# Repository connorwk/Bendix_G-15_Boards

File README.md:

# Bendix G-15 Boards
KiCad re-creations of the schematics and boards for the Bendix G-15.

These boards are meant to be functional drop in replacements for the original boards, whether they are damaged or missing.
The idea is either:
- To drill out the rivets on the original card's frames, desolder the wires for the tube sockets/etc and rivet/solder in the new board.
- Build up oragami PCBs to build a card frame.

Currently the goal is to get all schematics and boards layed out for the G-15 CPU and get a CPU at the System Source Computer Museum up and running using replacement boards.

## TODO
- Find suitable replacement diodes/transistors. This will be determined by component parameter analysis, specification comparison, and functional testing of boards with replaced components.
- Add oragami PCBs to allow building your own card handles to assemble around the boards.

## References
Documentation for the Bendix G-15 can be found here:
http://bitsavers.org/pdf/bendix/g-15/

The document used for schematics is:
http://bitsavers.org/pdf/bendix/g-15/G15D_Tech_Man_Rev1_Part1.pdf

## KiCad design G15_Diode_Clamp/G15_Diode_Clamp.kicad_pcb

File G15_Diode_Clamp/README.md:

# Diode ClamP, For Bendix G-15 CPU
[Schematic](G15_Diode_Clamp_Schematic.pdf)

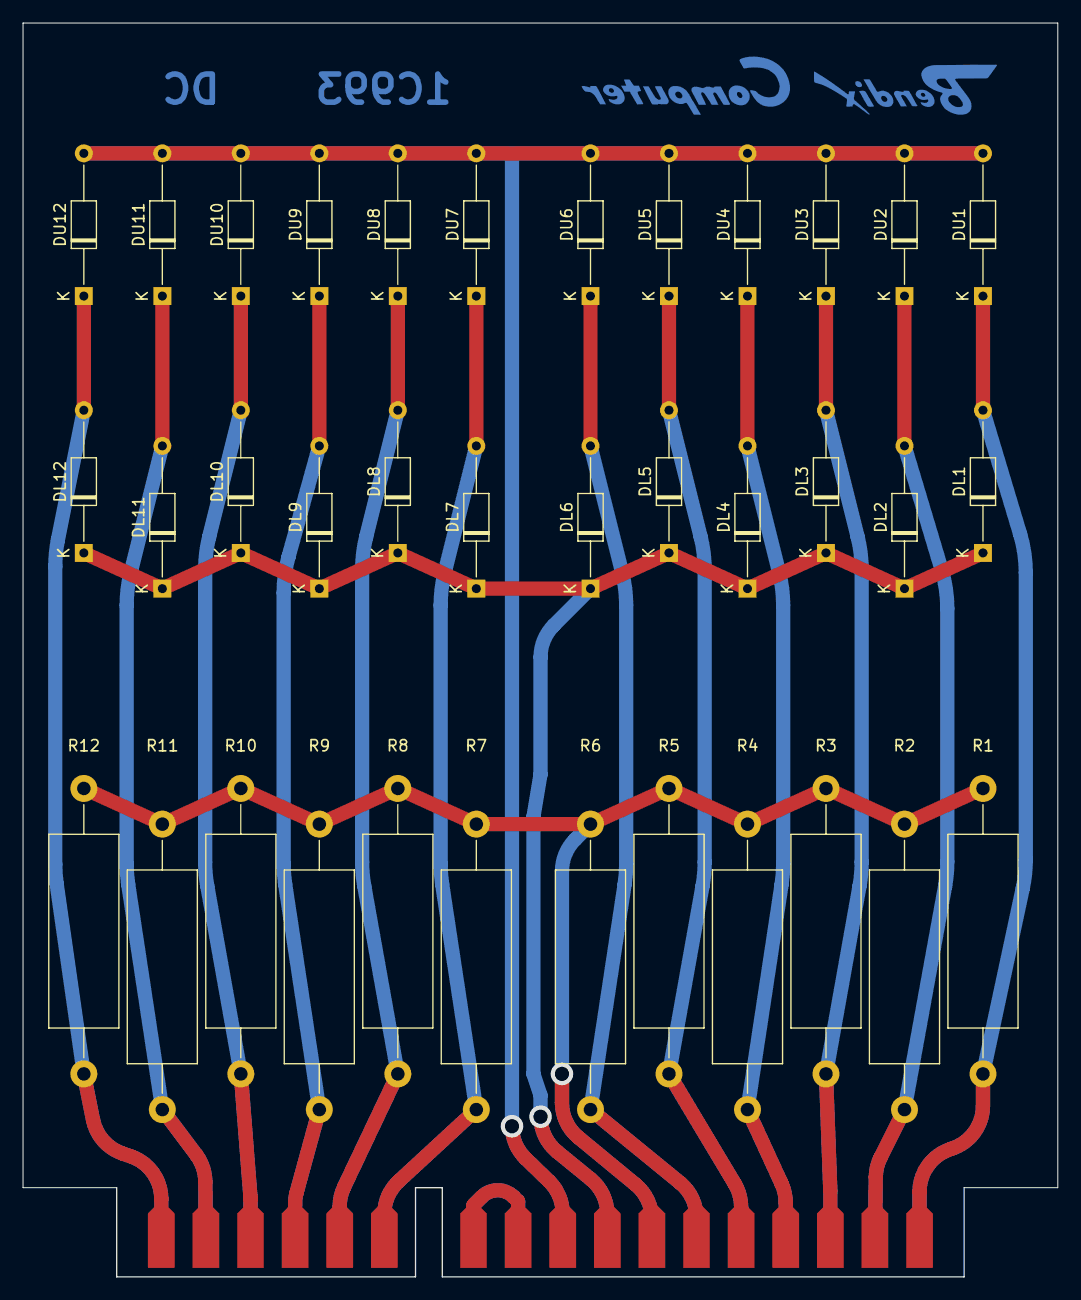
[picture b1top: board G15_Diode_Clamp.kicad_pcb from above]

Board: 2 copper layers, 92.1 x 111.6 mm, 37 parts (0 on the bottom side), 17 nets.

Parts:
DL1, DL2, DL3, DL4, DL5, DL6, DL7, DL8, DL9, DL10, DL11, DL12: 1N4007; D_DO-35_SOD27_P12.70mm_Horizontal
DU1, DU2, DU3, DU4, DU5, DU6, DU7, DU8, DU9, DU10, DU11, DU12: 1N4007; D_DO-35_SOD27_P12.70mm_Horizontal
J1: Conn_02x18_Row_Letter_First; Card_Edge_N_Key
R1, R2, R3, R4, R5, R6, R7, R8, R9, R10, R11, R12: 39K 1W 5%; R_Axial_DIN0617_L17.0mm_D6.0mm_P25.40mm_Horizontal

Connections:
/+100V: J1.a7, J1.b7, R1.2, R2.2, R3.2, R4.2, R5.2, R6.2, R7.2, R8.2, R9.2, R10.2, R11.2, R12.2
/-20V: DU1.2 (A), DU2.2 (A), DU3.2 (A), DU4.2 (A), DU5.2 (A), DU6.2 (A), DU7.2 (A), DU8.2 (A), DU9.2 (A), DU10.2 (A), DU11.2 (A), DU12.2 (A), J1.a9, J1.b9
/CL_{1}: DL1.2 (A), DU1.1 (K), J1.a1, J1.b1, R1.1
/CL_{2}: DL2.2 (A), DU2.1 (K), J1.a2, J1.b2, R2.1
/CL_{3}: DL3.2 (A), DU3.1 (K), J1.a3, J1.b3, R3.1
/CL_{4}: DL4.2 (A), DU4.1 (K), J1.a4, J1.b4, R4.1
/CL_{5}: DL5.2 (A), DU5.1 (K), J1.a5, J1.b5, R5.1
/CL_{6}: DL6.2 (A), DU6.1 (K), J1.a6, J1.b6, R6.1
/CL_{7}: DL7.2 (A), DU7.1 (K), J1.a13, J1.b13, R7.1
/CL_{8}: DL8.2 (A), DU8.1 (K), J1.a14, J1.b14, R8.1
/CL_{9}: DL9.2 (A), DU9.1 (K), J1.a15, J1.b15, R9.1
/CL_{10}: DL10.2 (A), DU10.1 (K), J1.a16, J1.b16, R10.1
/CL_{11}: DL11.2 (A), DU11.1 (K), J1.a17, J1.b17, R11.1
/CL_{12}: DL12.2 (A), DU12.1 (K), J1.a18, J1.b18, R12.1
GND: DL1.1 (K), DL2.1 (K), DL3.1 (K), DL4.1 (K), DL5.1 (K), DL6.1 (K), DL7.1 (K), DL8.1 (K), DL9.1 (K), DL10.1 (K), DL11.1 (K), DL12.1 (K), J1.a8, J1.b8
unnamed: J1.a10, J1.a11
unnamed: J1.b10, J1.b11

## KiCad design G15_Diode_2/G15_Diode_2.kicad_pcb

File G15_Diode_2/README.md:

# Diode 2, For Bendix G-15 CPU
[Schematic](G15_Diode_2_Schematic.pdf)

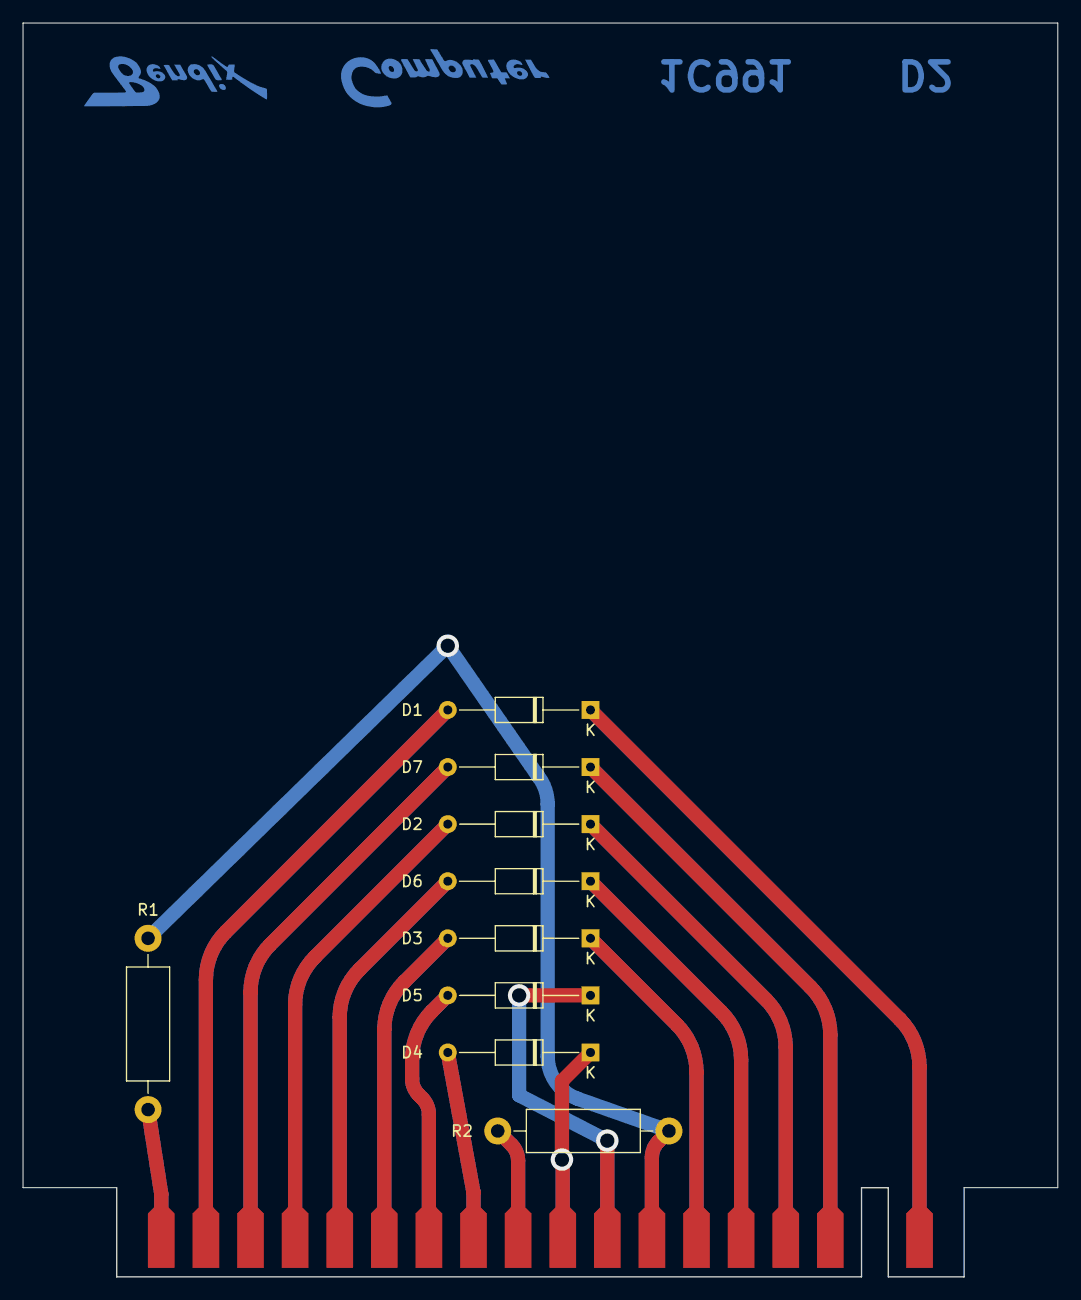
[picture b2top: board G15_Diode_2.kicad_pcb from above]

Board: 2 copper layers, 92.1 x 111.6 mm, 10 parts (0 on the bottom side), 17 nets.

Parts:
D1, D2, D3, D4, D5, D6, D7: 1N4007; D_DO-35_SOD27_P12.70mm_Horizontal
J1: Conn_02x18_Row_Letter_First; Card_Edge_B_Key
R1, R2: 110K 1/2W 5%; R_Axial_DIN0411_L9.9mm_D3.6mm_P15.24mm_Horizontal

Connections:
/110K to B+_{1}: J1.a18, J1.b18, R1.1
/110K to B+_{2}: J1.a10, J1.b10, R2.1
/+100V: J1.a7, J1.b7, R1.2, R2.2
/C_{1}: D1.1 (K), J1.a1, J1.b1
/C_{2}: D2.1 (K), J1.a4, J1.b4
/C_{3}: D3.1 (K), J1.a6, J1.b6
/C_{4}: D4.1 (K), J1.a9, J1.b9
/C_{5}: D5.1 (K), J1.a8, J1.b8
/C_{6}: D6.1 (K), J1.a5, J1.b5
/C_{7}: D7.1 (K), J1.a3, J1.b3
/P_{1}: D1.2 (A), J1.a17, J1.b17
/P_{2}: D2.2 (A), J1.a15, J1.b15
/P_{3}: D3.2 (A), J1.a13, J1.b13
/P_{4}: D4.2 (A), J1.a11, J1.b11
/P_{5}: D5.2 (A), J1.a12, J1.b12
/P_{6}: D6.2 (A), J1.a14, J1.b14
/P_{7}: D7.2 (A), J1.a16, J1.b16

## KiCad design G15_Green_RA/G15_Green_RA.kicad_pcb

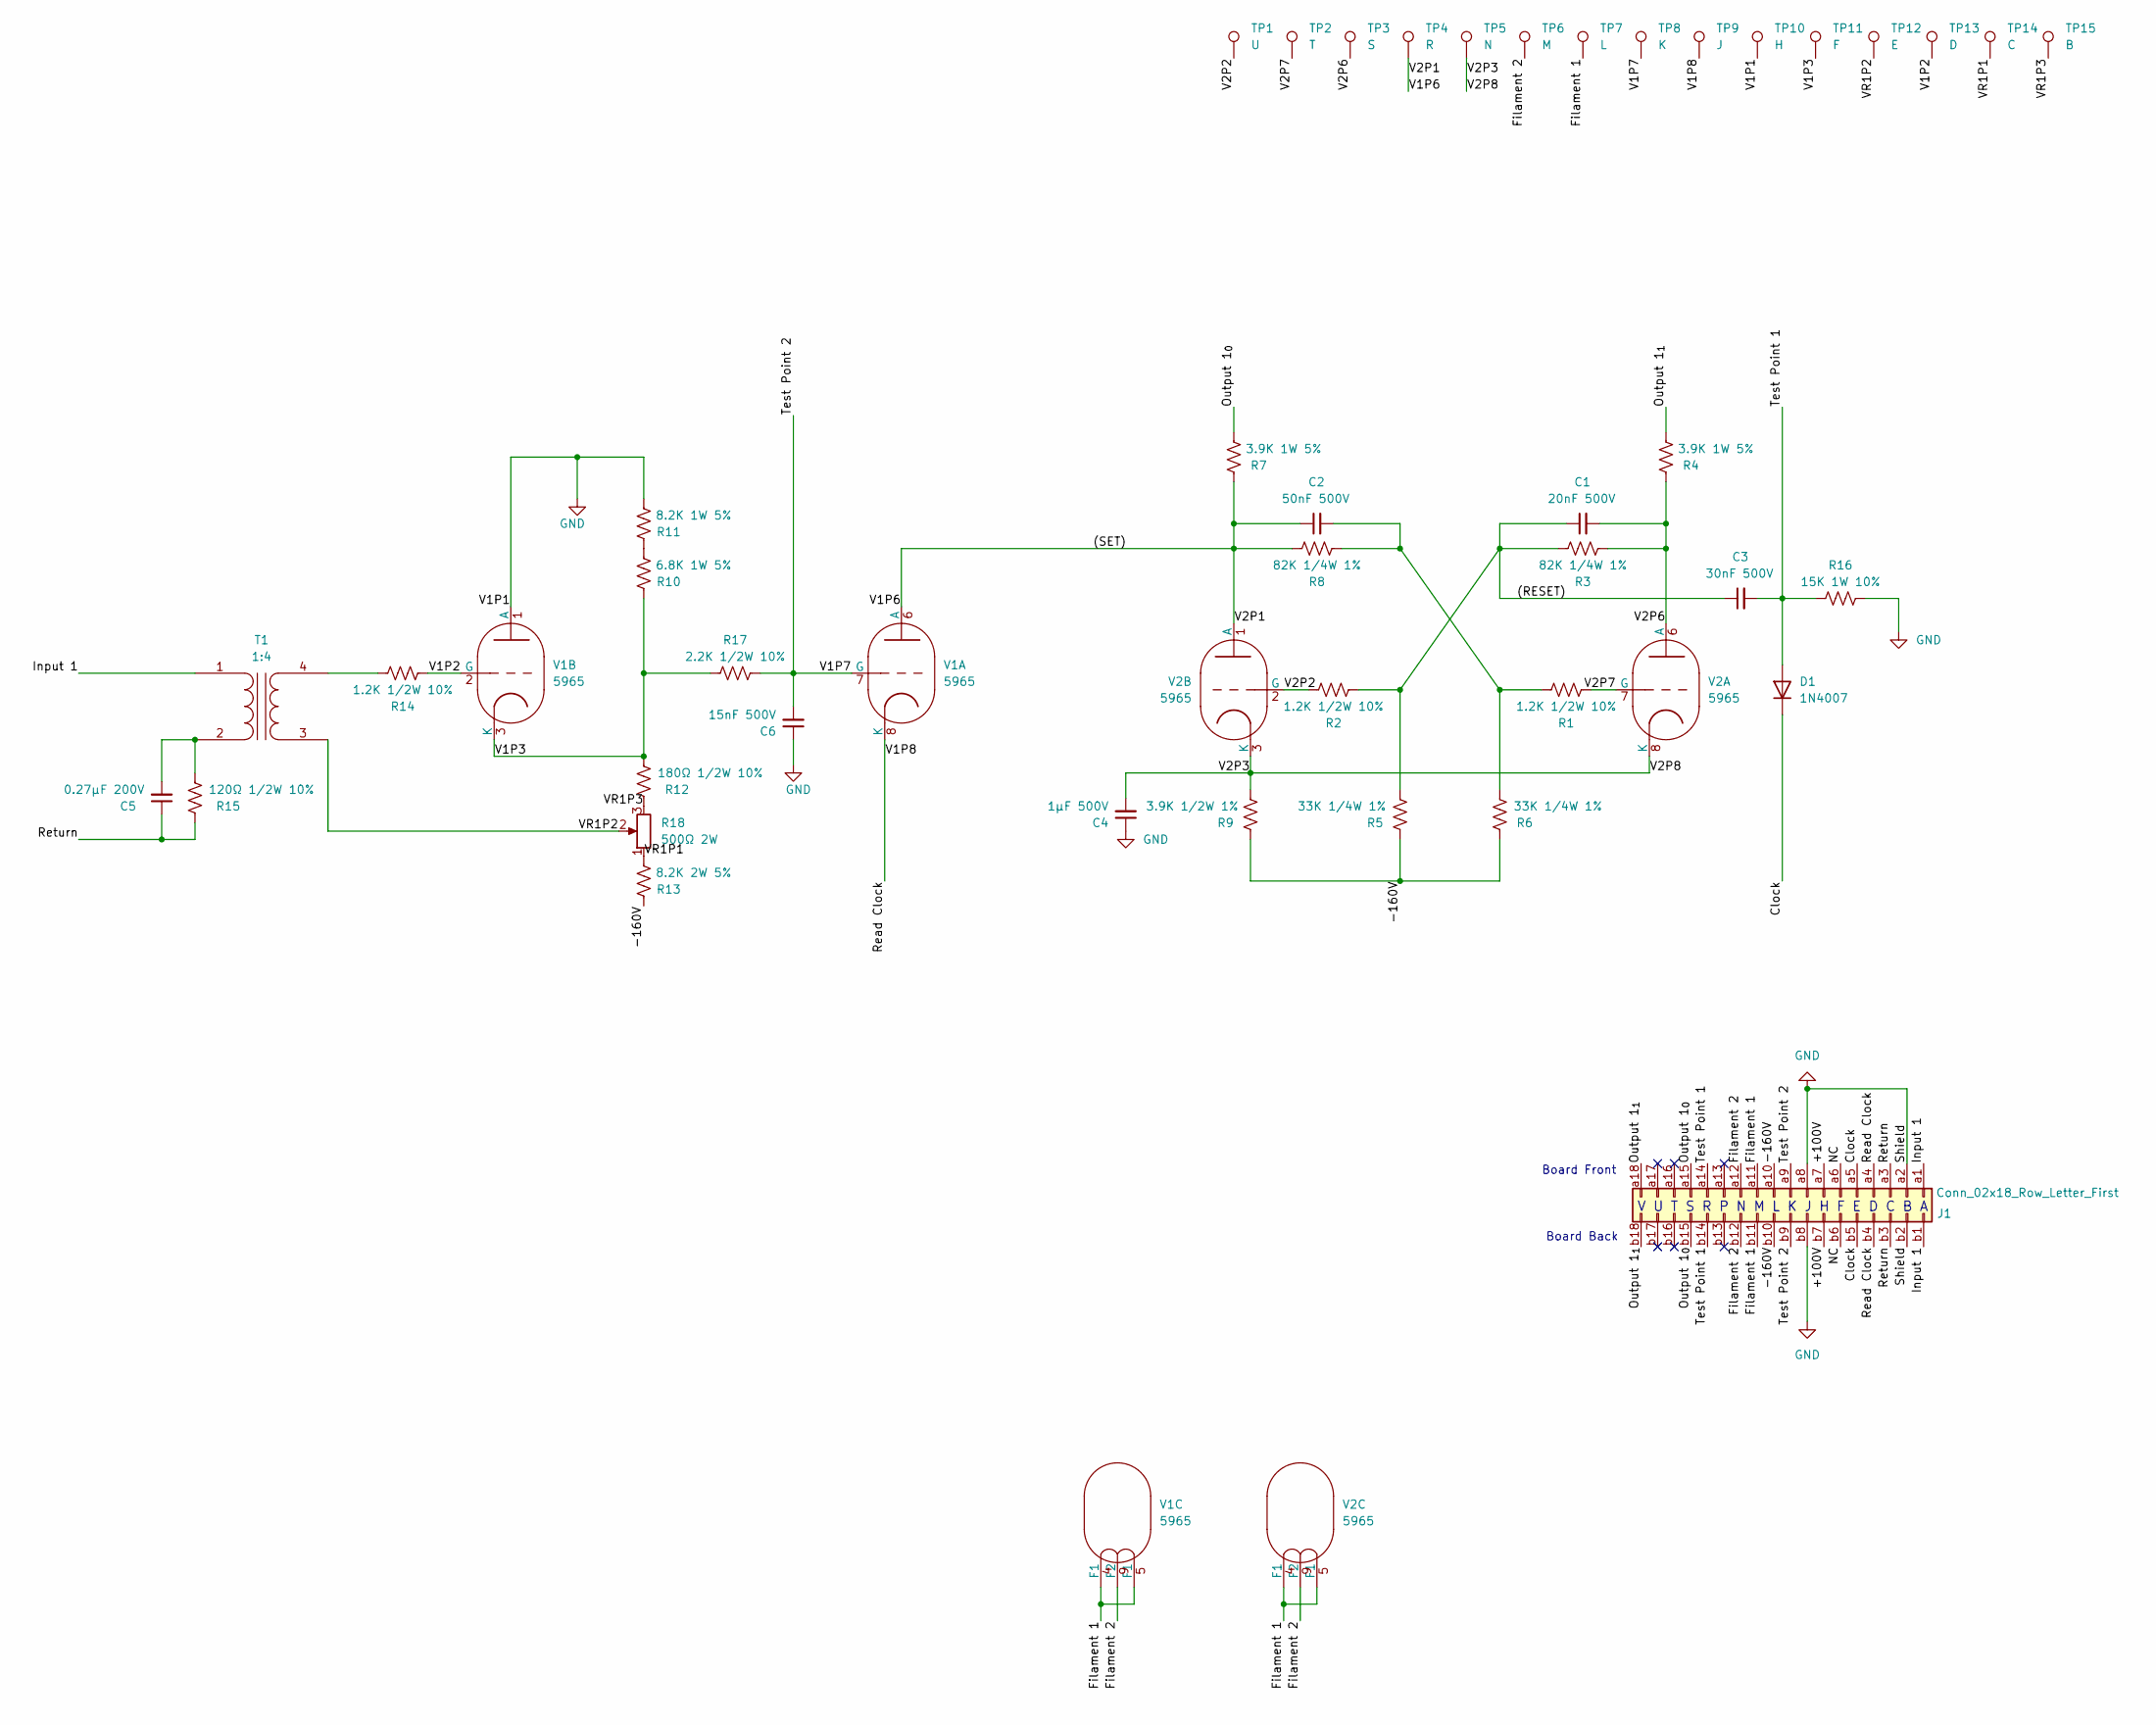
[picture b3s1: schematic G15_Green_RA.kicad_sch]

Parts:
C1: 20nF 500V; C_Axial_L12.0mm_D6.5mm_P20.00mm_Horizontal
C2: 50nF 500V; C_Axial_L12.0mm_D6.5mm_P20.00mm_Horizontal
C3: 30nF 500V; C_Axial_L12.0mm_D6.5mm_P20.00mm_Horizontal
C4: 1µF 500V; C_Axial_L12.0mm_D6.5mm_P20.00mm_Horizontal
C5: 0.27µF 200V; C_Axial_L22.0mm_D10.5mm_P27.50mm_Horizontal
C6: 15nF 500V; C_Axial_L12.0mm_D6.5mm_P20.00mm_Horizontal
D1: 1N4007; D_DO-35_SOD27_P12.70mm_Horizontal
J1: Conn_02x18_Row_Letter_First; Card_Edge_F_Key
R1, R2, R14: 1.2K 1/2W 10%; R_Axial_DIN0411_L9.9mm_D3.6mm_P15.24mm_Horizontal
R3, R8: 82K 1/4W 1%; R_Axial_DIN0516_L15.5mm_D5.0mm_P20.32mm_Horizontal
R4, R7: 3.9K 1W 5%; R_Axial_DIN0516_L15.5mm_D5.0mm_P20.32mm_Horizontal
R5, R6: 33K 1/4W 1%; R_Axial_DIN0516_L15.5mm_D5.0mm_P20.32mm_Horizontal
R9: 3.9K 1/2W 1%; R_Axial_DIN0617_L17.0mm_D6.0mm_P25.40mm_Horizontal
R10: 6.8K 1W 5%; R_Axial_DIN0516_L15.5mm_D5.0mm_P20.32mm_Horizontal
R11: 8.2K 1W 5%; R_Axial_DIN0516_L15.5mm_D5.0mm_P20.32mm_Horizontal
R12: 180Ω 1/2W 10%; R_Axial_DIN0411_L9.9mm_D3.6mm_P15.24mm_Horizontal
R13: 8.2K 2W 5%; R_Axial_DIN0918_L18.0mm_D9.0mm_P22.86mm_Horizontal
R15: 120Ω 1/2W 10%; R_Axial_DIN0411_L9.9mm_D3.6mm_P15.24mm_Horizontal
R16: 15K 1W 10%; R_Axial_DIN0614_L14.3mm_D5.7mm_P25.40mm_Horizontal
R17: 2.2K 1/2W 10%; R_Axial_DIN0411_L9.9mm_D3.6mm_P15.24mm_Horizontal
R18: 500Ω 2W
T1: 1:4; Transformer_Toroid_Horizontal_D14.0mm_Amidon-T50
TP1: U; TestPoint_Plated_Hole_D2.0mm
TP2: T; TestPoint_Plated_Hole_D2.0mm
TP3: S; TestPoint_Plated_Hole_D2.0mm
TP4: R; TestPoint_Plated_Hole_D2.0mm
TP5: N; TestPoint_Plated_Hole_D2.0mm
TP6: M; TestPoint_Plated_Hole_D2.0mm
TP7: L; TestPoint_Plated_Hole_D2.0mm
TP8: K; TestPoint_Plated_Hole_D2.0mm
TP9: J; TestPoint_Plated_Hole_D2.0mm
TP10: H; TestPoint_Plated_Hole_D2.0mm
TP11: F; TestPoint_Plated_Hole_D2.0mm
TP12: E; TestPoint_Plated_Hole_D2.0mm
TP13: D; TestPoint_Plated_Hole_D2.0mm
TP14: C; TestPoint_Plated_Hole_D2.0mm
TP15: B; TestPoint_Plated_Hole_D2.0mm
V1, V2: 5965

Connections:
/(RESET): C1.1, C3.1, R2.1, R3.2, R5.1
/(SET): C2.1, R7.2, R8.2, TP4.1, V1.6 (A), V2.1 (A)
/+100V: J1.a7, J1.b7
/-160V: J1.a10, J1.b10, R5.2, R6.2, R9.2, R13.2
/Clock: D1.1 (K), J1.a5, J1.b5
/Filament 1: J1.a11, J1.b11, TP7.1, V1.4 (F1), V1.5 (F1), V2.4 (F1), V2.5 (F1)
/Filament 2: J1.a12, J1.b12, TP6.1, V1.9 (F2), V2.9 (F2)
/Input 1: J1.a1, J1.b1, T1.1 (AA)
/Output 1_{0}: J1.a15, J1.b15, R7.1
/Output 1_{1}: J1.a18, J1.b18, R4.1
/Read Clock: J1.a4, J1.b4, TP9.1, V1.8 (K)
/Return: C5.1, J1.a3, J1.b3, R15.2
/Test Point 1: C3.2, D1.2 (A), J1.a14, J1.b14, R16.1
/V1P2: R14.1, TP13.1, V1.2 (G)
/V1P3: R10.2, R12.1, R17.1, TP11.1, V1.3 (K)
/V1P7: C6.2, J1.a9, J1.b9, R17.2, TP8.1, V1.7 (G)
/V2P2: R2.2, TP1.1, V2.2 (G)
/V2P3: C4.2, R9.1, TP5.1, V2.3 (K), V2.8 (K)
/V2P6: C1.2, R3.1, R4.2, TP3.1, V2.6 (A)
/V2P7: R1.1, TP2.1, V2.7 (G)
/VR1P1: R13.1, R18.1, TP14.1
/VR1P2: R18.2, T1.3 (SA), TP12.1
/VR1P3: R12.2, R18.3, TP15.1
GND: C4.1, C6.1, J1.a2, J1.a8, J1.b2, J1.b8, R11.1, R16.2, TP10.1, V1.1 (A)
unnamed: C2.2, R1.2, R6.1, R8.1
unnamed: C5.2, R15.1, T1.2 (AB)
unnamed: R10.1, R11.2
unnamed: R14.2, T1.4 (SB)

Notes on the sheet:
Board Back
Board Front
V U T S R P N M L K J H F E D C B A

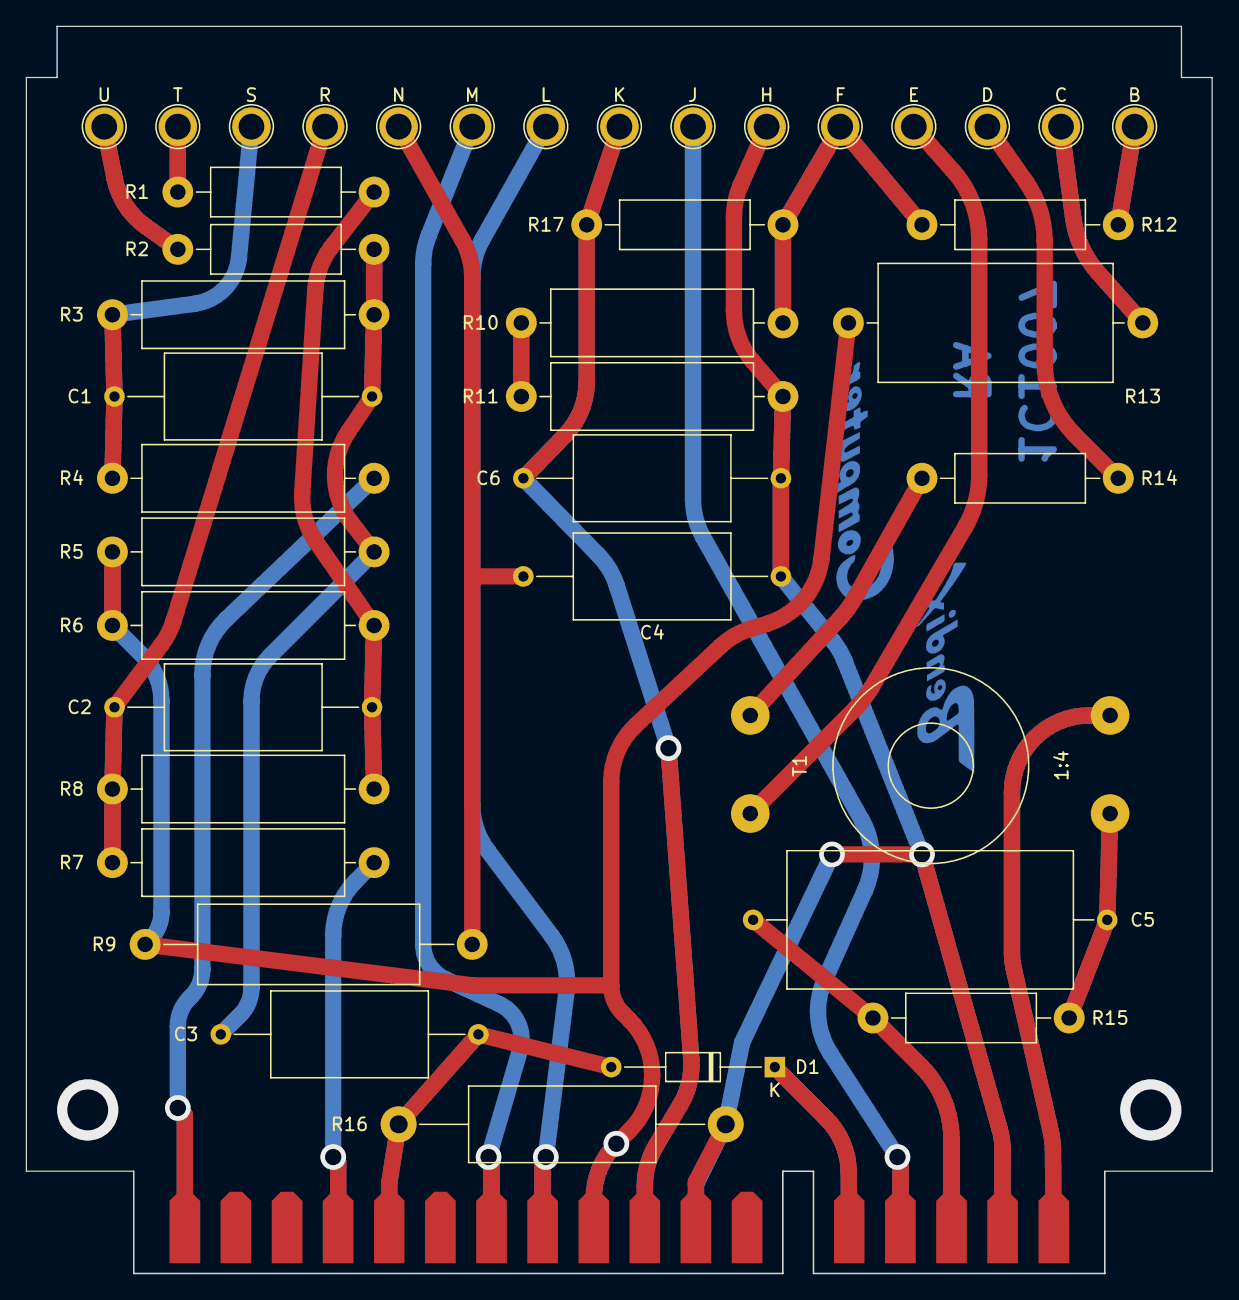
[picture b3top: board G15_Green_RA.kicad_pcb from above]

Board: 2 copper layers, 92.1 x 96.8 mm, 41 parts (0 on the bottom side), 28 nets.

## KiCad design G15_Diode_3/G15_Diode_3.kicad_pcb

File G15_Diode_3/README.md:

# Diode 3, For Bendix G-15 CPU
[Schematic](G15_Diode_3_Schematic.pdf)

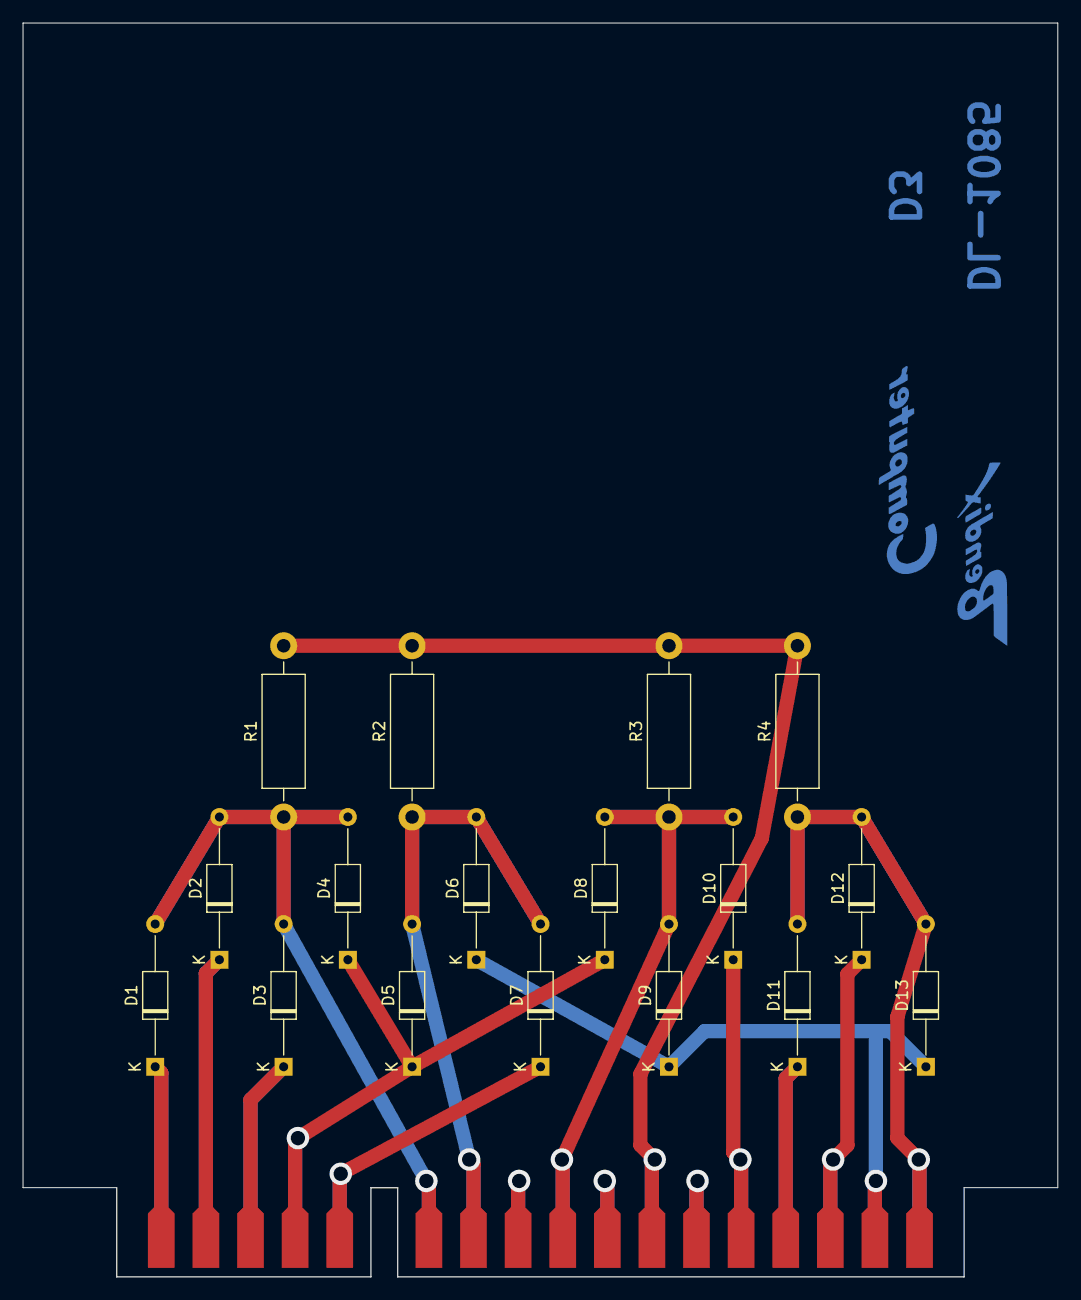
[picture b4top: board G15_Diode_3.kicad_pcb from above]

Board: 2 copper layers, 92.1 x 111.6 mm, 18 parts (0 on the bottom side), 17 nets.

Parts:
D1, D2, D3, D4, D5, D6, D7, D8, D9, D10, D11, D12, D13: 1N4007; D_DO-35_SOD27_P12.70mm_Horizontal
J1: Conn_02x18_Row_Letter_First; Card_Edge_P_Key
R1, R2, R3, R4: 110K 1/2W 5%; R_Axial_DIN0411_L9.9mm_D3.6mm_P15.24mm_Horizontal

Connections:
/+100V: J1.a7, J1.b7, R1.2, R2.2, R3.2, R4.2
/C_{1}: D1.1 (K), J1.a18, J1.b18
/C_{2}: D2.1 (K), J1.a17, J1.b17
/C_{3}: D3.1 (K), J1.a16, J1.b16
/C_{4,5,8}: D4.1 (K), D5.1 (K), D8.1 (K), J1.a15, J1.b15
/C_{6,9,13}: D6.1 (K), D9.1 (K), D13.1 (K), J1.a2, J1.b2
/C_{7}: D7.1 (K), J1.a14, J1.b14
/C_{10}: D10.1 (K), J1.a5, J1.b5
/C_{11}: D11.1 (K), J1.a4, J1.b4
/C_{12}: D12.1 (K), J1.a3, J1.b3
/NC1: J1.a10, J1.b10
/NC2: J1.a8, J1.b8
/NC3: J1.a6, J1.b6
/P_{1,2,3,4}: D1.2 (A), D2.2 (A), D3.2 (A), D4.2 (A), J1.a12, J1.b12, R1.1
/P_{5,6,7}: D5.2 (A), D6.2 (A), D7.2 (A), J1.a11, J1.b11, R2.1
/P_{8,9,10}: D8.2 (A), D9.2 (A), D10.2 (A), J1.a9, J1.b9, R3.1
/P_{11,12,13}: D11.2 (A), D12.2 (A), D13.2 (A), J1.a1, J1.b1, R4.1

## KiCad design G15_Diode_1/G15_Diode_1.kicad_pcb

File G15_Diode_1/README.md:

# Diode 1, For Bendix G-15 CPU
[Schematic](G15_Diode_1_Schematic.pdf)

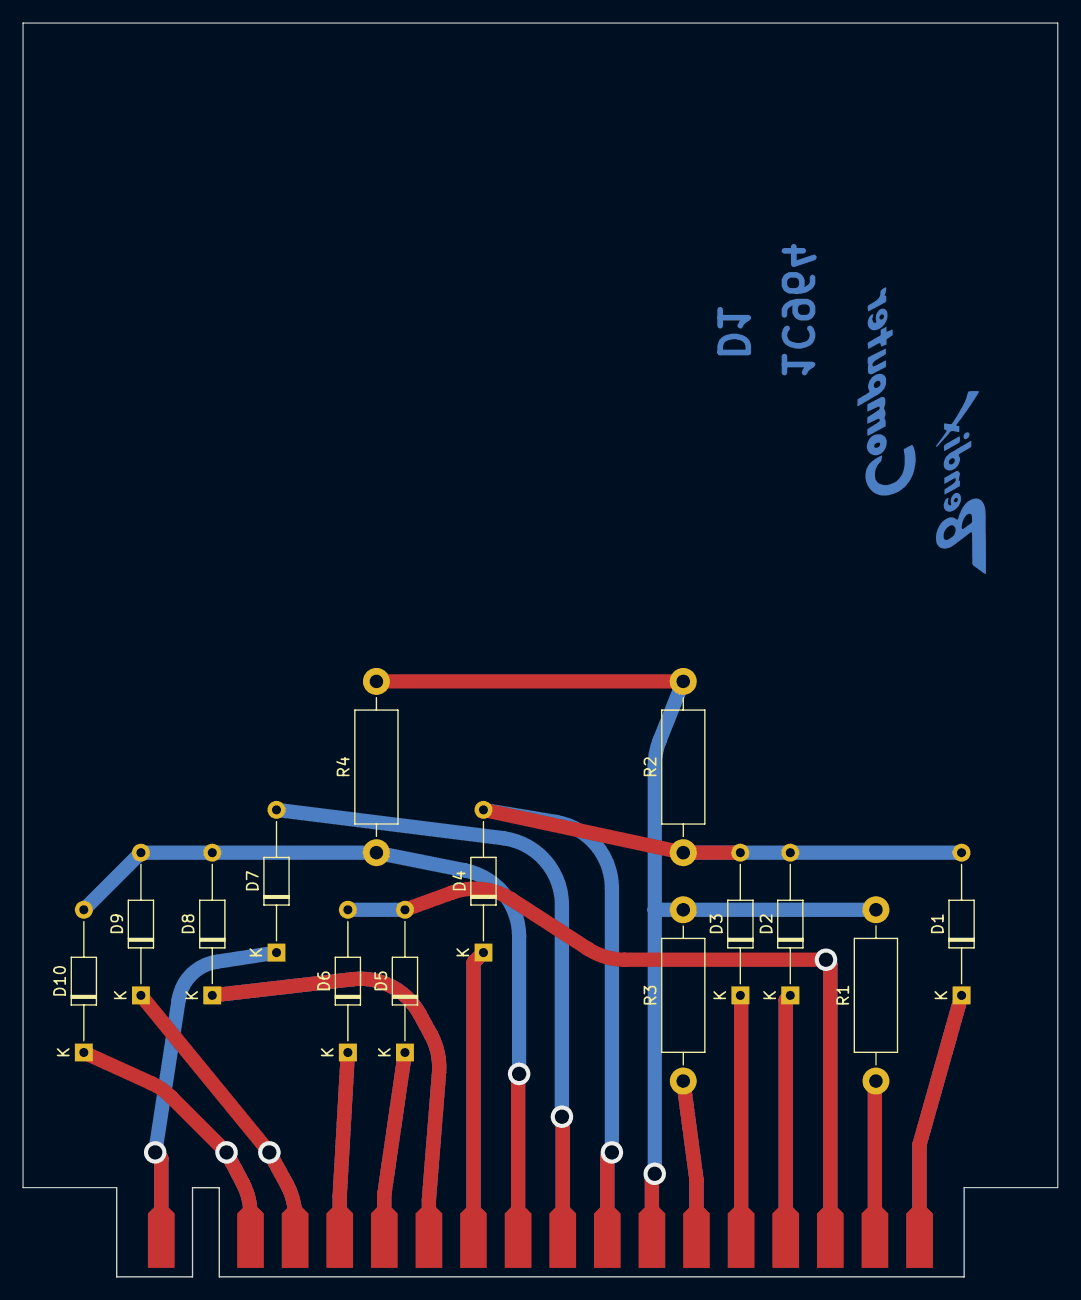
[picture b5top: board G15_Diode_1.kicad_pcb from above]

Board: 2 copper layers, 92.1 x 111.6 mm, 15 parts (0 on the bottom side), 17 nets.

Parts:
D1, D2, D3, D4, D5, D6, D7, D8, D9, D10: 1N4007; D_DO-35_SOD27_P12.70mm_Horizontal
J1: Conn_02x18_Row_Letter_First; Card_Edge_U_Key
R1, R2, R4: 110K 1/2W 5%; R_Axial_DIN0411_L9.9mm_D3.6mm_P15.24mm_Horizontal
R3: 150K 1/2W 5%; R_Axial_DIN0411_L9.9mm_D3.6mm_P15.24mm_Horizontal

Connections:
/110K to B+: J1.a2, J1.b2, R1.1
/150K to B+: J1.a6, J1.b6, R3.1
/+100V: J1.a7, J1.b7, R1.2, R2.2, R3.2, R4.2
/C_{1}: D1.1 (K), J1.a1, J1.b1
/C_{2}: D2.1 (K), J1.a4, J1.b4
/C_{3}: D3.1 (K), J1.a5, J1.b5
/C_{4}: D4.1 (K), J1.a11, J1.b11
/C_{5}: D5.1 (K), J1.a13, J1.b13
/C_{6}: D6.1 (K), J1.a14, J1.b14
/C_{7}: D7.1 (K), J1.a18, J1.b18
/C_{8}: D8.1 (K), J1.a12, J1.b12
/C_{9}: D9.1 (K), J1.a15, J1.b15
/C_{10}: D10.1 (K), J1.a16, J1.b16
/P_{1,2,3,4}: D1.2 (A), D2.2 (A), D3.2 (A), D4.2 (A), J1.a8, J1.b8, R2.1
/P_{5,6}: D5.2 (A), D6.2 (A), J1.a3, J1.b3
/P_{7}: D7.2 (A), J1.a9, J1.b9
/P_{8,9,10}: D8.2 (A), D9.2 (A), D10.2 (A), J1.a10, J1.b10, R4.1

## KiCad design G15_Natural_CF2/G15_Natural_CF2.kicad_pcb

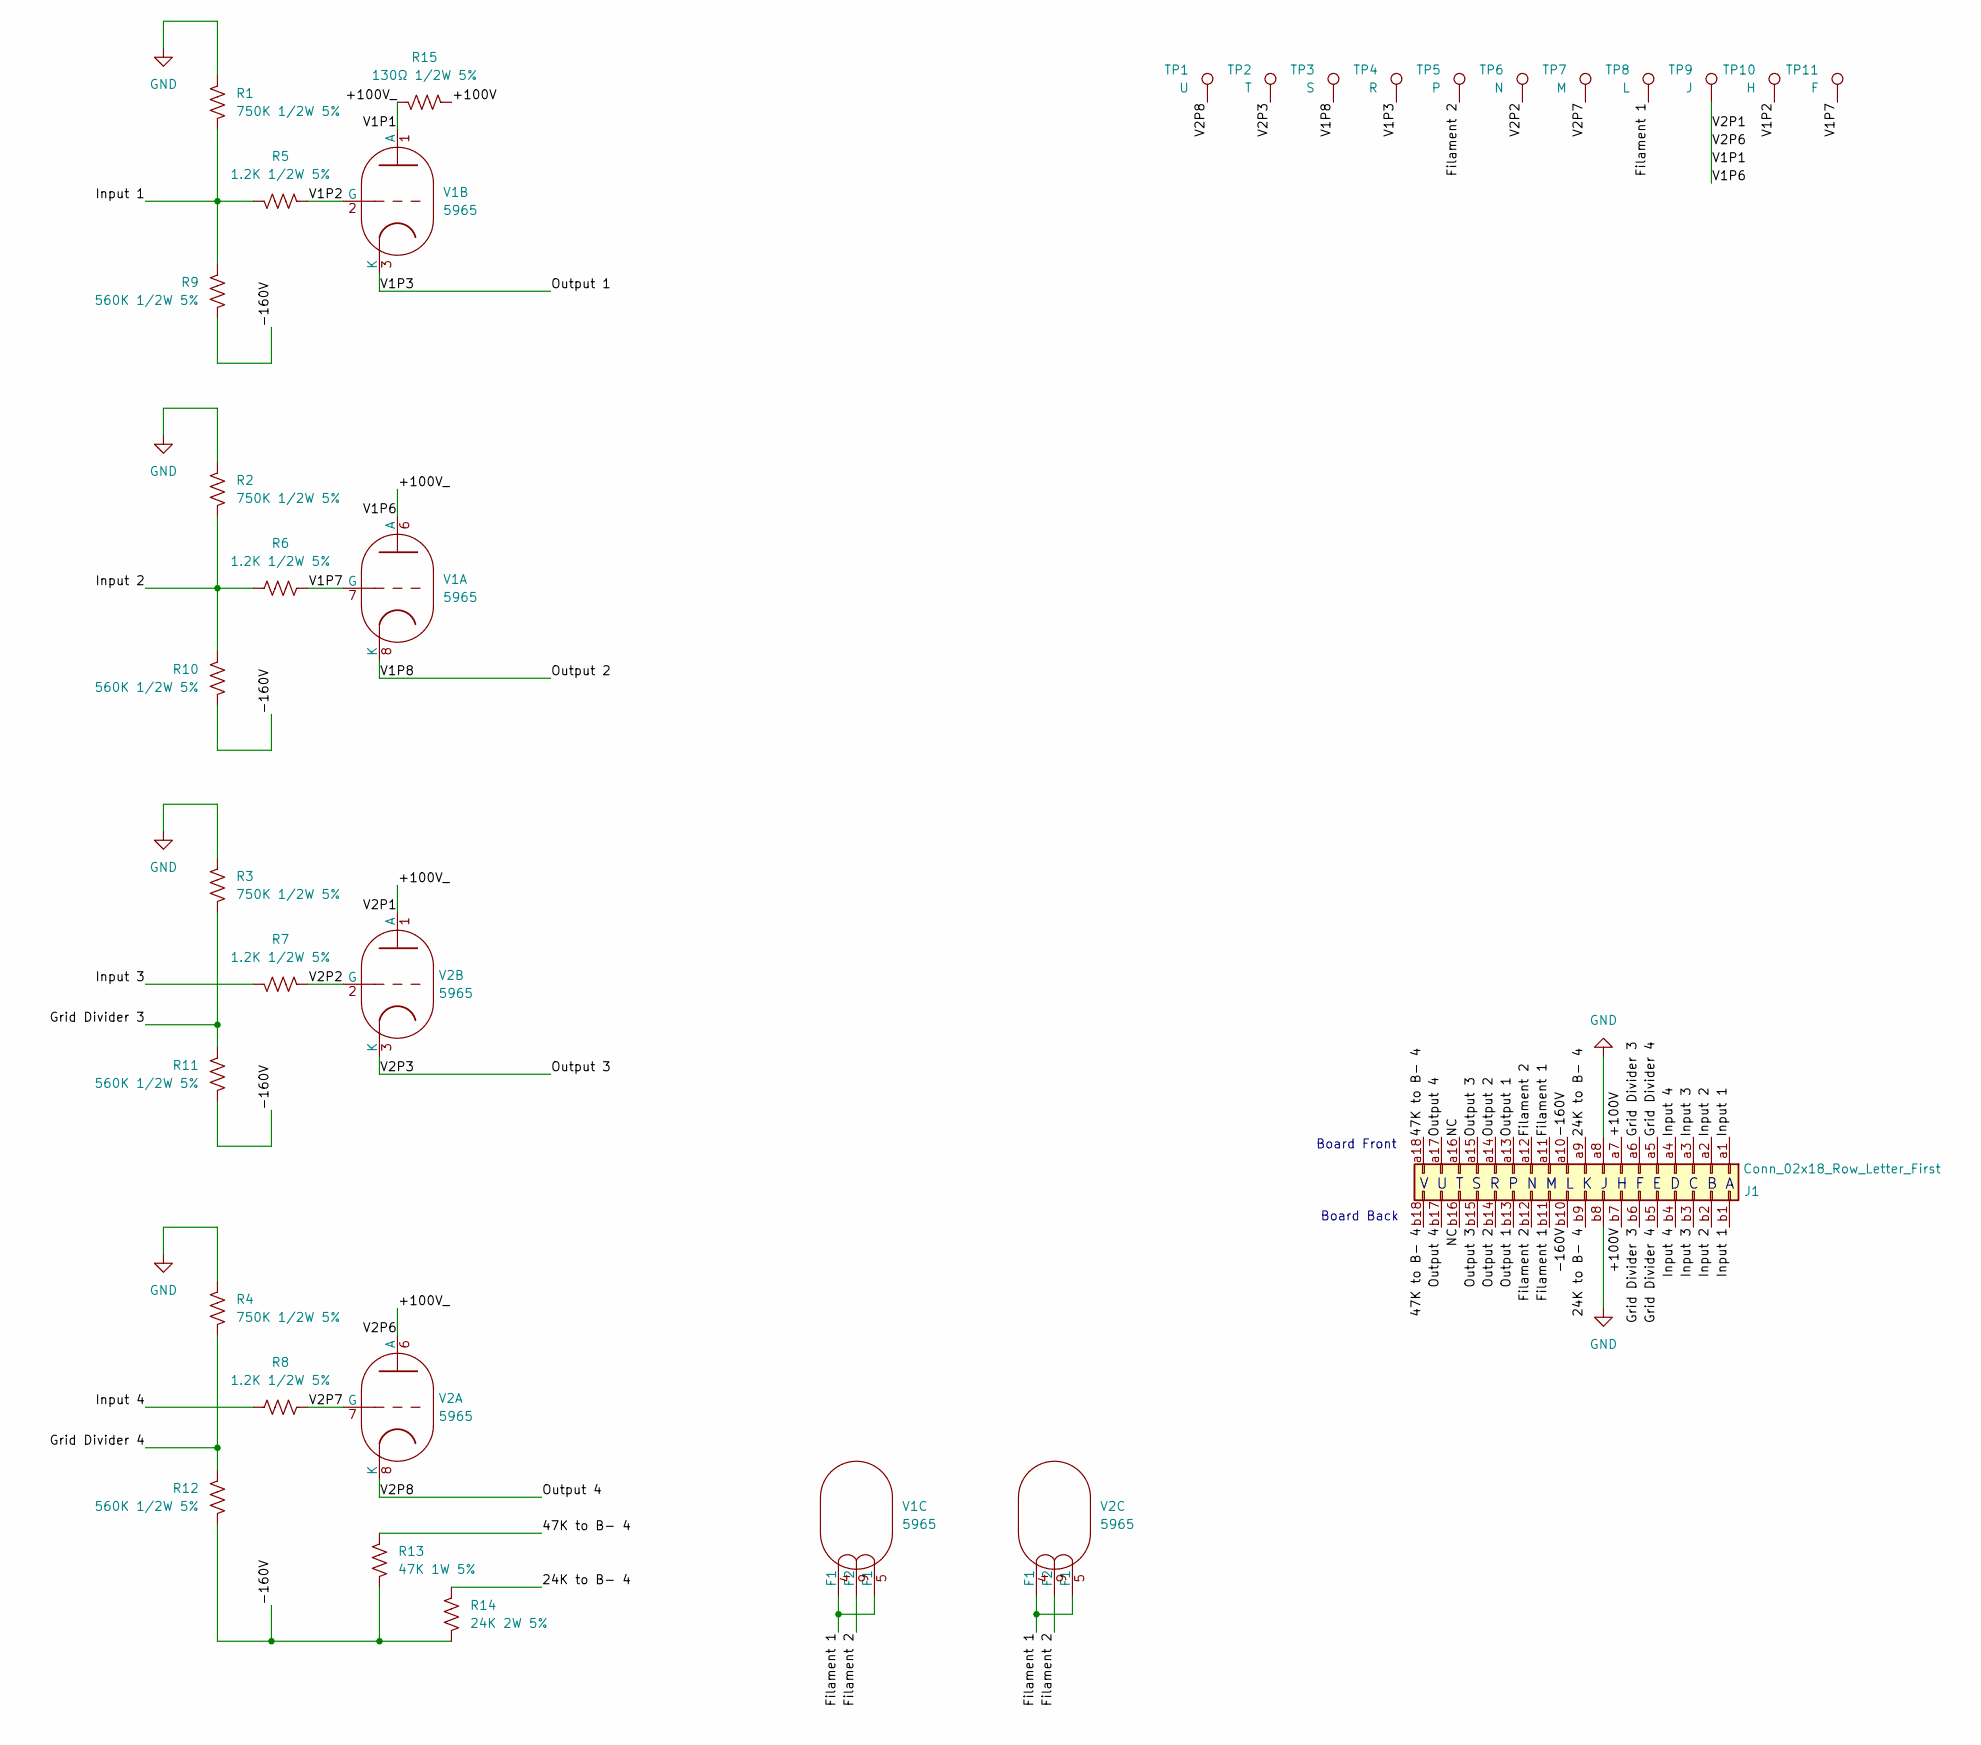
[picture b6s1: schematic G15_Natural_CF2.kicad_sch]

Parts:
J1: Conn_02x18_Row_Letter_First; Card_Edge_T_Key
R1, R2, R3, R4: 750K 1/2W 5%; R_Axial_DIN0309_L9.0mm_D3.2mm_P15.24mm_Horizontal
R5, R6, R7, R8: 1.2K 1/2W 5%; R_Axial_DIN0309_L9.0mm_D3.2mm_P15.24mm_Horizontal
R9, R10, R11, R12: 560K 1/2W 5%; R_Axial_DIN0309_L9.0mm_D3.2mm_P15.24mm_Horizontal
R13: 47K 1W 5%; R_Axial_DIN0516_L15.5mm_D5.0mm_P20.32mm_Horizontal
R14: 24K 2W 5%; R_Axial_DIN0918_L18.0mm_D9.0mm_P25.40mm_Horizontal
R15: 130Ω 1/2W 5%; R_Axial_DIN0309_L9.0mm_D3.2mm_P15.24mm_Horizontal
TP1: U; TestPoint_Plated_Hole_D2.0mm
TP2: T; TestPoint_Plated_Hole_D2.0mm
TP3: S; TestPoint_Plated_Hole_D2.0mm
TP4: R; TestPoint_Plated_Hole_D2.0mm
TP5: P; TestPoint_Plated_Hole_D2.0mm
TP6: N; TestPoint_Plated_Hole_D2.0mm
TP7: M; TestPoint_Plated_Hole_D2.0mm
TP8: L; TestPoint_Plated_Hole_D2.0mm
TP9: J; TestPoint_Plated_Hole_D2.0mm
TP10: H; TestPoint_Plated_Hole_D2.0mm
TP11: F; TestPoint_Plated_Hole_D2.0mm
V1, V2: 5965

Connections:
/24K to B- 4: J1.a9, J1.b9, R14.1
/47K to B- 4: J1.a18, J1.b18, R13.1
/+100V: J1.a7, J1.b7, R15.2
/+100V_: R15.1, TP9.1, V1.1 (A), V1.6 (A), V2.1 (A), V2.6 (A)
/-160V: J1.a10, J1.b10, R9.1, R10.1, R11.1, R12.1, R13.2, R14.2
/Filament 1: J1.a11, J1.b11, TP8.1, V1.4 (F1), V1.5 (F1), V2.4 (F1), V2.5 (F1)
/Filament 2: J1.a12, J1.b12, TP5.1, V1.9 (F2), V2.9 (F2)
/Grid Divider 3: J1.a6, J1.b6, R3.2, R11.2
/Grid Divider 4: J1.a5, J1.b5, R4.2, R12.2
/Input 1: J1.a1, J1.b1, R1.2, R5.1, R9.2
/Input 2: J1.a2, J1.b2, R2.2, R6.2, R10.2
/Input 3: J1.a3, J1.b3, R7.1
/Input 4: J1.a4, J1.b4, R8.2
/Output 1: J1.a13, J1.b13, TP4.1, V1.3 (K)
/Output 2: J1.a14, J1.b14, TP3.1, V1.8 (K)
/Output 3: J1.a15, J1.b15, TP2.1, V2.3 (K)
/Output 4: J1.a17, J1.b17, TP1.1, V2.8 (K)
/V1P2: R5.2, TP10.1, V1.2 (G)
/V1P7: R6.1, TP11.1, V1.7 (G)
/V2P2: R7.2, TP6.1, V2.2 (G)
/V2P7: R8.1, TP7.1, V2.7 (G)
GND: J1.a8, J1.b8, R1.1, R2.1, R3.1, R4.1

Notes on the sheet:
Board Back
Board Front
V U T S R P N M L K J H F E D C B A

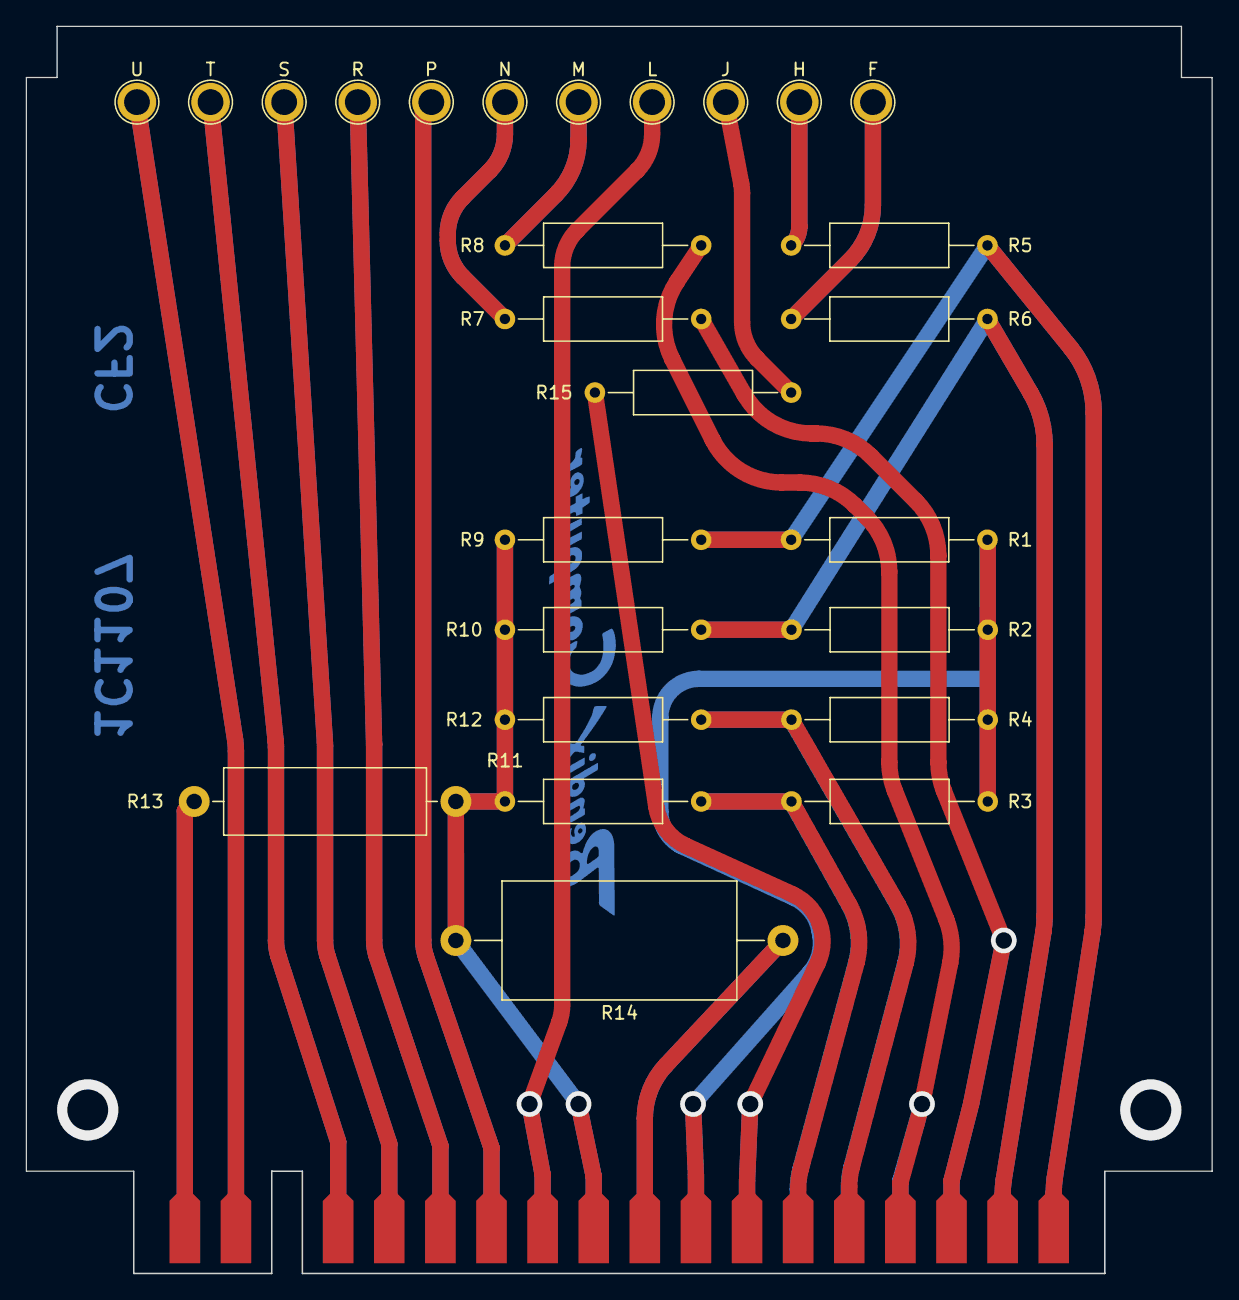
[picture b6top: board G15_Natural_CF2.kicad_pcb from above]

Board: 2 copper layers, 92.1 x 96.8 mm, 27 parts (0 on the bottom side), 22 nets.
